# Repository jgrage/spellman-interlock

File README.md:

# Spellman Interlock PCB
Interlock PCB for Spellman MNX and µXMAN High Voltage supplies

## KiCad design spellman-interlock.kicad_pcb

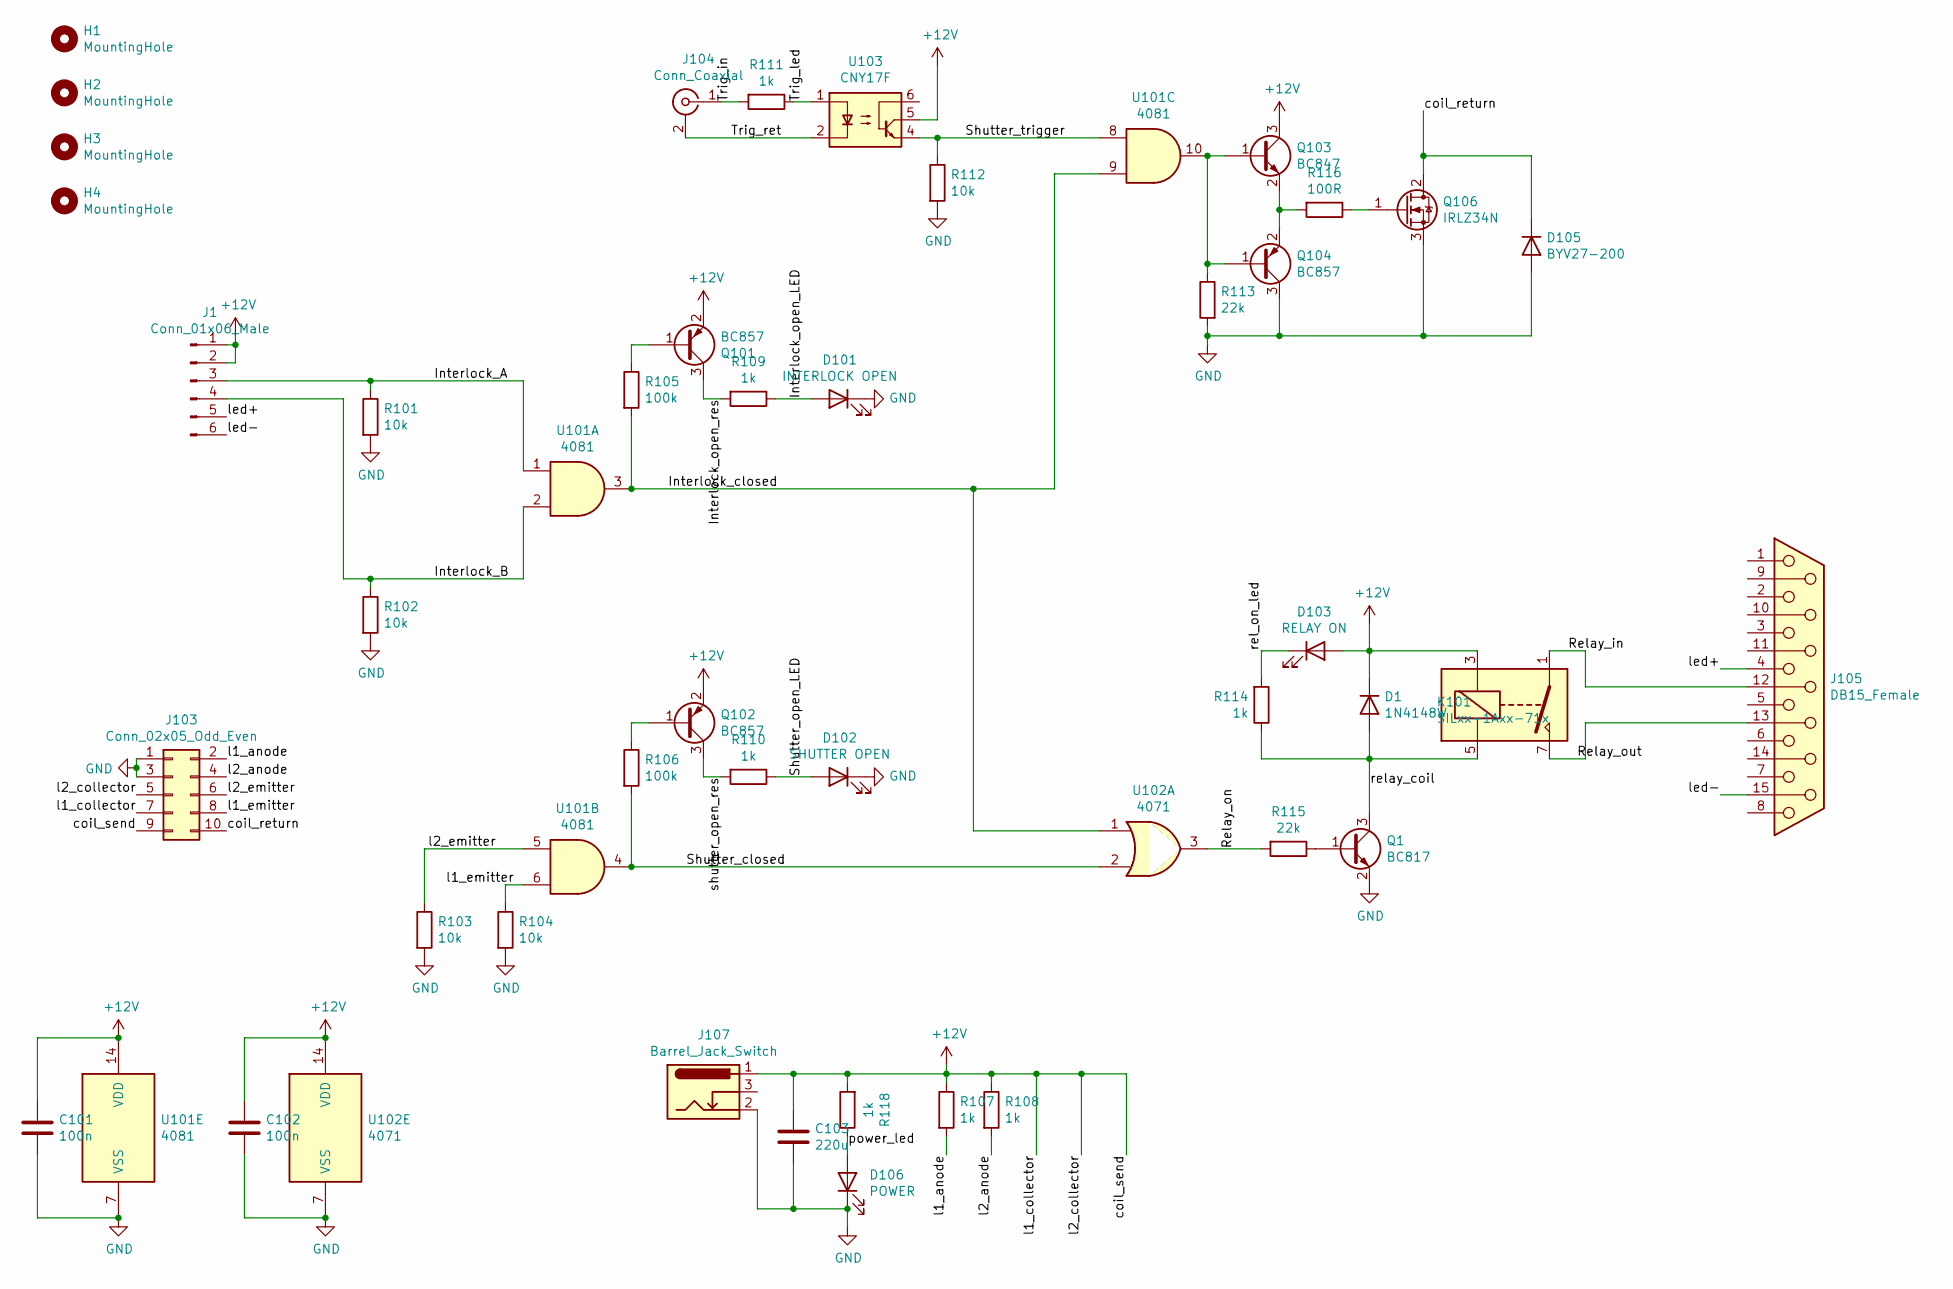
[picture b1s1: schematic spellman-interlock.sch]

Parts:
C101, C102: 100n; C_0603_1608Metric; LCSC C14663
C103: 220u; CP_EIA-7343-43_Kemet-X; LCSC C7231
D1: 1N4148W; D_SOD-123; LCSC C81598
D101: INTERLOCK OPEN; LED_0805_2012Metric_Pad1.15x1.40mm_HandSolder
D102: SHUTTER OPEN; LED_0805_2012Metric_Pad1.15x1.40mm_HandSolder
D103: RELAY ON; LED_0805_2012Metric_Pad1.15x1.40mm_HandSolder
D105: BYV27-200; D_5W_P5.08mm_Vertical_AnodeUp
D106: POWER; LED_0805_2012Metric_Pad1.15x1.40mm_HandSolder
H1, H2, H3, H4: MountingHole; MountingHole_2.2mm_M2_DIN965
J1: Conn_01x06_Male; Molex_PicoBlade_53261-0671_1x06-1MP_P1.25mm_Horizontal
J103: Conn_02x05_Odd_Even; PinHeader_2x05_P2.54mm_Horizontal
J104: Conn_Coaxial; BNC_Amphenol_B6252HB-NPP3G-50_Horizontal
J105: DB15_Female; DSUB-15_Female_Horizontal_P2.77x2.84mm_EdgePinOffset7.70mm_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
J107: Barrel_Jack_Switch; BarrelJack_Wuerth_6941xx301002
K101: SILxx-1Axx-71x; Relay_SPST_StandexMeder_SIL_Form1A
Q1: BC817; SOT-23; LCSC C52801
Q101, Q102, Q104: BC857; SOT-23; LCSC C8666
Q103: BC847; SOT-23; LCSC C8664
Q106: IRLZ34N; TO-220-3_Horizontal_TabDown
R101, R102, R103, R104, R112: 10k; R_0603_1608Metric; LCSC C25804
R105, R106: 100k; R_0603_1608Metric; LCSC C25803
R107, R108, R109, R110, R111, R114, R118: 1k; R_1206_3216Metric; LCSC C4410
R113, R115: 22k; R_0603_1608Metric; LCSC C31850
R116: 100R; R_0603_1608Metric; LCSC C22775
U101: 4081; SO-14_3.9x8.65mm_P1.27mm; LCSC C40551
U102: 4071; SO-14_3.9x8.65mm_P1.27mm; LCSC C28869
U103: CNY17F; DIP-6_W8.89mm_SMDSocket_LongPads; LCSC C142631

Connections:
+12V: C101.1, C102.1, C103.1, D1.1 (K), D103.2 (A), J1.1, J1.2, J103.5, J103.7, J103.9, J107.1, K101.3, Q101.2 (E), Q102.2 (E), Q103.3 (C), R107.1, R108.1, R118.2, U101.14 (VDD), U102.14 (VDD), U103.5
/Interlock_A: J1.3, R101.1, U101.1
/Interlock_B: J1.4, R102.1, U101.2
/Interlock_closed: R105.2, U101.3, U101.9, U102.1
/Interlock_open_LED: D101.2 (A), R109.1
/Interlock_open_res: Q101.3 (C), R109.2
/Relay_in: J105.12, K101.1
/Relay_on: R115.2, U102.3
/Relay_out: J105.13, K101.7
/Shutter_closed: R106.2, U101.4, U102.2
/Shutter_open_LED: D102.2 (A), R110.1
/Shutter_trigger: R112.1, U101.8, U103.4
/Trig_in: J104.1 (In), R111.2
/Trig_led: R111.1, U103.1
/Trig_ret: J104.2 (Ext), U103.2
/coil_return: D105.1 (K), J103.10, Q106.2 (D)
/l1_anode: J103.2, R107.2
/l1_emitter: J103.8, R104.1, U101.6
/l2_anode: J103.4, R108.2
/l2_emitter: J103.6, R103.1, U101.5
/led+: J1.5, J105.4
/led-: J1.6, J105.15
/power_led: D106.2 (A), R118.1
/rel_on_led: D103.1 (K), R114.2
/relay_coil: D1.2 (A), K101.5, Q1.3 (C), R114.1
/shutter_open_res: Q102.3 (C), R110.2
GND: C101.2, C102.2, C103.2, D101.1 (K), D102.1 (K), D105.2 (A), D106.1 (K), J103.1, J103.3, J107.2, Q1.2 (E), Q104.3 (C), Q106.3 (S), R101.2, R102.2, R103.2, R104.2, R112.2, R113.2, U101.7 (VSS), U102.7 (VSS)
unnamed: Q1.1 (B), R115.1
unnamed: Q101.1 (B), R105.1
unnamed: Q102.1 (B), R106.1
unnamed: Q103.1 (B), Q104.1 (B), R113.1, U101.10
unnamed: Q103.2 (E), Q104.2 (E), R116.2
unnamed: Q106.1 (G), R116.1

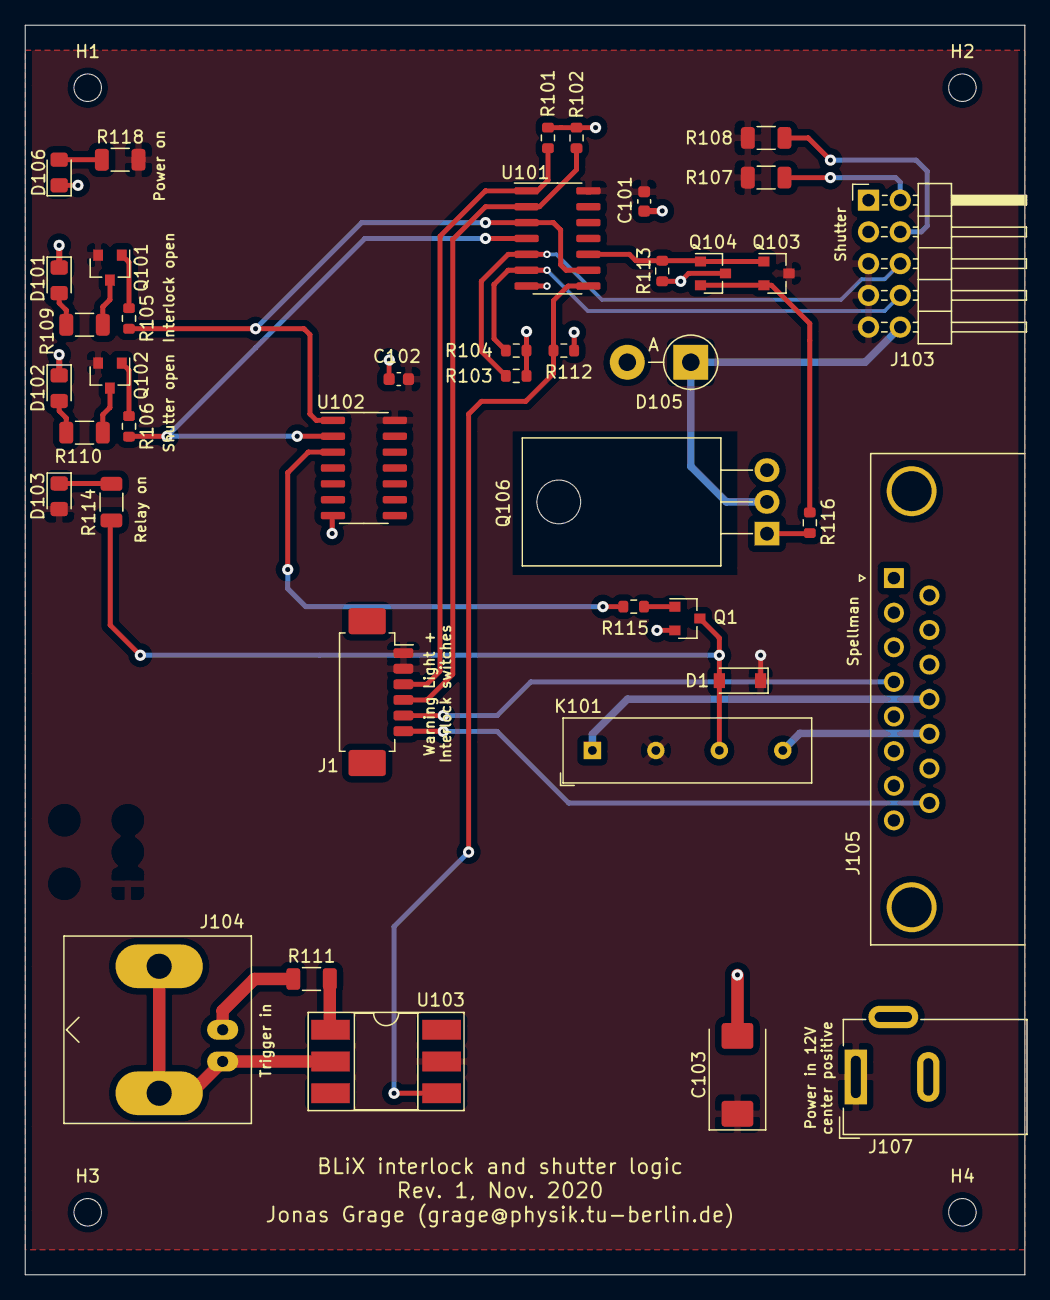
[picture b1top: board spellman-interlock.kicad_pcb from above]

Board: 2 copper layers, 80.0 x 100.0 mm, 45 parts (0 on the bottom side), 33 nets.
